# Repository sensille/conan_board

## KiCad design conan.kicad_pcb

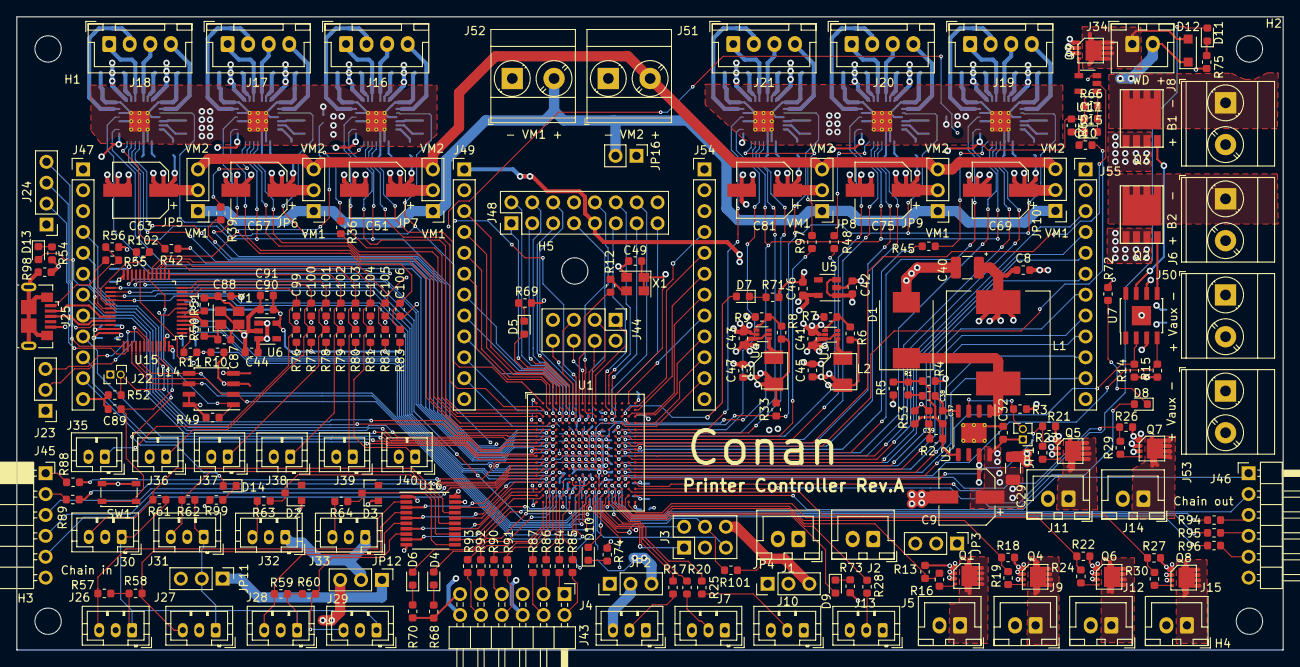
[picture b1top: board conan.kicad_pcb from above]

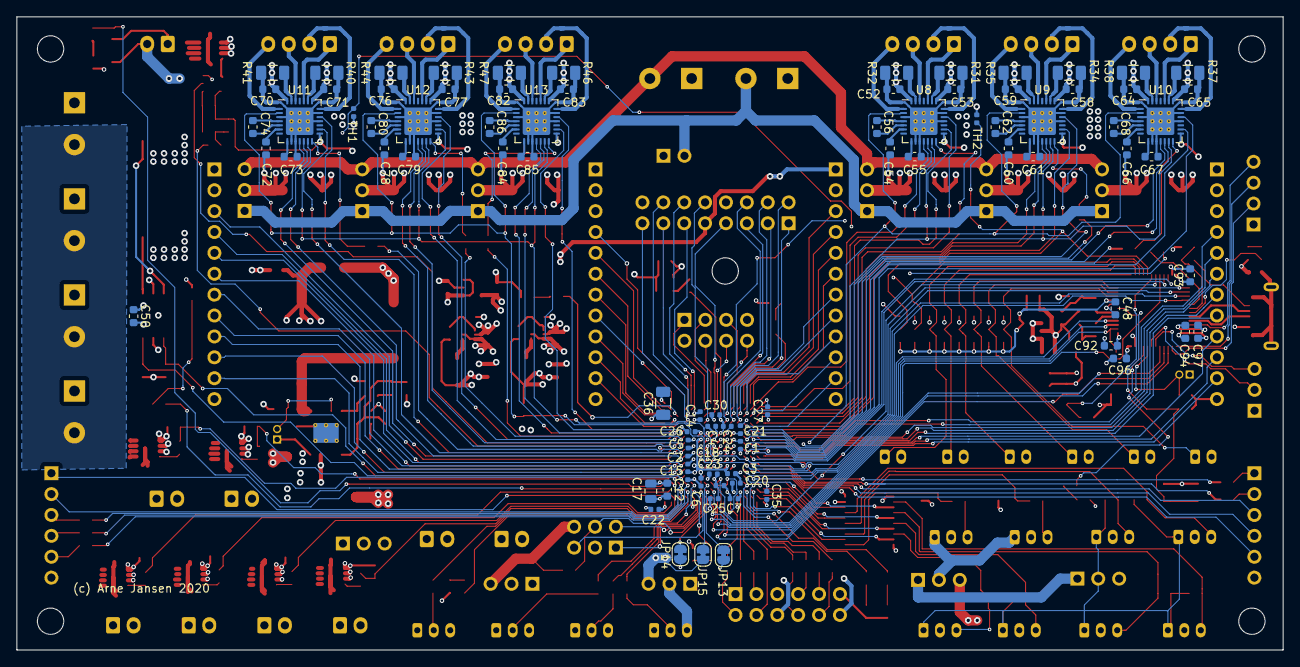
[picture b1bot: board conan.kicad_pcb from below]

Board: 4 copper layers, 154.0 x 77.0 mm, 320 parts (83 on the bottom side), 338 nets.

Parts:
C1, C2, C3, C4, C5, C6, C7, C14, C15, C21, C35: 10nF; C_0402_1005Metric
C8, C10, C11, C12, C42, C44, C46, C48, C91: 1uF; C_0603_1608Metric
C9, C51, C57, C63, C69, C75, C81: 100uF/50V/lowESR; CP_Elec_6.3x5.9
C17: 10uF; C_0805_2012Metric
C18, C20, C22, C23, C24, C25, C26, C27, C30: 100nF; C_0402_1005Metric
C29: 10uF/ceramic/50V/8mOhm; C_1206_3216Metric
C32: 220nF/50V; C_0603_1608Metric
C36: 22uF; C_1206_3216Metric
C37: 1.2nF; C_0603_1608Metric
C38: 68nF; C_0603_1608Metric
C39: 15nF; C_0603_1608Metric
C40: 68uF/tantalum/6.3V/100mOhm; C_1210_3225Metric
C41, C43: 4.7uF/10V/ceramic; C_0603_1608Metric
C45, C47: 22uF/6.3V/4mOhm/ceramic; C_0603_1608Metric
C49, C90: 10nF; C_0603_1608Metric
C50, C92, C93, C94, C96: 100nF; C_0603_1608Metric
C52, C53, C58, C59, C64, C65, C70, C71, C76, C77, C82, C83: 100nF/50V; C_0603_1608Metric
C54, C60, C66, C72, C78, C84: 100nF/16V; C_0603_1608Metric
C55, C61, C67, C73, C79, C85, C99, C100, C101, C102, C103, C104, C105, C106: 2.2uF; C_0603_1608Metric
C56, C62, C68, C74, C80, C86: 22nF/50V; C_0603_1608Metric
C87, C88: 10pF; C_0603_1608Metric
C89: 0.1uF; C_0603_1608Metric
C97: 4.7uF; C_0603_1608Metric
D1: MBRS540T3G; D_SMC
D2, D3: 5V; D_SOT-23_ANK
D4, D5, D6, D7, D8, D9, D10, D11, D13, D14: LED; LED_0603_1608Metric
D12: DSS12UTR; D_SOD-123F
D15: CDBU40; D_0603_1608Metric
H1, H2, H3, H4, H5: MountingHole; MountingHole_3.2mm_M3
J1, J2, J5, J9, J11, J12, J14, J15, J34: JST XH 2; JST_XH_B02B-XH-A_1x02_P2.50mm_Vertical
J3: PinH 2x3; PinHeader_2x03_P2.54mm_Vertical
J4, J7, J10, J13, J26, J27, J28, J29, J30, J31, J32, J33: JST PH 3; JST_PH_B3B-PH-K_1x03_P2.00mm_Vertical
J6, J8, J50, J51, J52, J53: ST 2; TerminalBlock_Phoenix_MKDS-3-2-5.08_1x02_P5.08mm_Horizontal
J16, J17, J18, J19, J20, J21: Stepper; JST_XH_B04B-XH-A_1x04_P2.50mm_Vertical
J22: PinHS 2; PinHeader_1x02_P1.27mm_Vertical
J23: PinH 3; PinHeader_1x03_P2.54mm_Vertical
J24: PinH 4; PinHeader_1x04_P2.54mm_Vertical
J25: USB_B_Micro; USB_Micro-B_GCT_USB3076-30-A
J35, J36, J37, J38, J39, J40: JST PH 2; JST_PH_B2B-PH-K_1x02_P2.00mm_Vertical
J43: PinH 2x6; PinHeader_2x06_P2.54mm_Horizontal
J44: ESP8266; PinHeader_2x04_P2.54mm_Vertical
J45: PinHHF 6; PinSocket_1x06_P2.54mm_Horizontal
J46: PinHH 6; PinHeader_1x06_P2.54mm_Horizontal
J47, J49, J54, J55: PinH 12; PinHeader_1x12_P2.54mm_Vertical
J48: PinH 2x8; PinHeader_2x08_P2.54mm_Vertical
JP1: Jumper_NC_Small; PinHeader_1x02_P1.27mm_Vertical
JP2, JP3, JP4, JP5, JP6, JP7, JP8, JP9, JP10, JP11, JP12: PinH 3; PinHeader_1x03_P2.54mm_Vertical
JP13, JP14, JP15: SolderJumper-2_P1.3mm_Bridged_RoundedPad1.0x1.5mm
JP16: PinH 2; PinHeader_1x02_P2.54mm_Vertical
L1: 22uH; L_Wuerth_WE-PD-Typ-LS
L2, L3: 1uH/10mOhm; SPM4012-LR
Q1, Q4, Q5, Q6, Q7, Q8, Q9: AON7524; FET_DGS_DFN3x3A_8L_EP1_P
Q2, Q3: TPH1R405PL; TPH1R405PL_SGD
R1: 1.1k; R_0603_1608Metric
R2: 240; R_0603_1608Metric
R3, R13, R14, R15, R18, R21, R22, R26, R27, R33, R65, R101: 10k; R_0603_1608Metric
R4: 5.1k; R_0603_1608Metric
R5: 680; R_0603_1608Metric
R6: 83.3k; R_0603_1608Metric
R7, R52: 100k; R_0603_1608Metric
R8: 435k; R_0603_1608Metric
R9: 97.6k; R_0603_1608Metric
R10, R11, R49, R76, R77, R78, R79, R80, R81, R82, R83: 4.7k; R_0603_1608Metric
R12, R16, R19, R23, R24, R29, R30, R84, R85, R86, R87, R88, R89, R90, R91, R92, R93, R94, R95, R96, R102: 22; R_0603_1608Metric
R17, R20, R25, R28: 220; R_0603_1608Metric
R31, R32, R34, R35, R37, R38, R40, R41, R43, R44, R46, R47: 100m; R_1206_3216Metric
R36, R39, R42, R45, R48, R54, R63, R64, R68, R69, R70, R71, R72, R73, R74, R75, R97, R99: 1k; R_0603_1608Metric
R50, R51: 0; R_0603_1608Metric
R53, R56: 220k; R_0603_1608Metric
R55: 330k; R_0603_1608Metric
R57, R58, R59, R60, R61, R62: 2.2k; R_0603_1608Metric
R66: 1M; R_0603_1608Metric
R98: 100; R_0603_1608Metric
SW1: Reset; SW_SPST_PTS810
TH1, TH2: NTC_100k; R_0402_1005Metric
U1: ECP5U12_CABGA256; BGA-256_14.0x14.0mm_Layout16x16_P0.8mm_Ball0.45mm_Pad0.32mm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
U2: L7986; HSOP-8-1EP_3.9x4.9mm_P1.27mm_EP2.41x3.1mm_ThermalVias
U3, U4: TLV62569; SOT-563
U5: LP5907MFX-2.5; SOT-23-5
U6: LP5907MFX-3.3; SOT-23-5
U7: MIC4127; SOIC-8-1EP_3.9x4.9mm_P1.27mm_EP2.35x2.35mm
U8, U9, U10, U11, U12, U13: TMC2209; QFN-28-1EP_5x5mm_P0.5mm_EP3.35x3.35mm_ThermalVias
U14: AT25xxx; SOIC-8_3.9x4.9mm_P1.27mm
U15: STM32F070CBTx; LQFP-48_7x7mm_P0.5mm
U16: 74VLX244; TSSOP-20_4.4x6.5mm_P0.65mm
U17: MC74VHC1G132; SOT-23-5
X1: ASE-50MHz; Oscillator_SMD_Abracon_ASE-4Pin_3.2x2.5mm
Y1: 16MHz; Crystal_SMD_SeikoEpson_TSX3225-4Pin_3.2x2.5mm

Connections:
+1V1: C1.1, C4.1, C7.1, C18.1, C20.1, C22.1, C23.1, C25.1, C45.1, L2.2, R6.1, U1.G6, U1.G7, U1.G9, U1.L8, U1.L9, U1.L10
+2V5: C3.1, C6.1, C12.1, C15.1, C17.1, C46.1, U1.G11, U1.L7, U5.5
+3V3: C2.1, C5.1, C11.1, C14.1, C21.1, C24.1, C26.1, C27.1, C30.1, C35.1, C36.1, C47.1, C49.1, C92.1, C93.1, C94.1, C96.1, C97.1, J3.6, J22.1, J43.6, J43.12, J44.7, J47.3, J48.16, J54.3, JP2.3, JP4.3, JP11.3, JP15.1, L3.2, R8.1, R10.2, R33.2, R49.1, R65.1, R66.1, R101.2, U1.F6, U1.F7, U1.F10, U1.F11, U1.H6, U1.H7, U1.H11, U1.J6, U1.J7, U1.J11, U1.K11, U1.L6, U1.L11, U8.15, U9.15, U10.15, U11.15, U12.15, U13.15, U14.3, U14.7, U14.8, U15.1, U15.24, U15.36, U15.48, U16.20, U17.5, X1.1, X1.4
+5V: C8.1, C39.1, C40.1, C41.1, C42.1, C43.1, C44.1, C50.1, D12.1, J1.1, J2.1, J34.2, J48.9, J49.1, J55.1, JP2.1, JP3.3, JP4.1, JP11.1, JP12.1, L1.2, R4.1, R53.1, U3.3, U3.5, U4.3, U4.5, U5.1, U5.3, U6.1, U6.3, U7.6
+VM1: J52.2, JP5.1, JP6.1, JP7.1, JP8.1, JP9.1, JP10.1, JP16.2
+VM2: J51.2, JP5.3, JP6.3, JP7.3, JP8.3, JP9.3, JP10.3
+Vaux: C9.1, C29.1, C32.1, J6.2, J8.2, J11.2, J14.2, J47.1, J50.2, J53.2, J54.1, JP1.1, JP3.1, JP12.3, JP16.1, U2.8
/FPGA/TCK: J3.4, R101.1, U1.T10
/FPGA/TDI: J3.2, U1.R11
/FPGA/TDO: J3.5, U1.M10
/FPGA/TMS: J3.1, U1.T11
/Stepper/Stepper 1/OA1: J18.1, U10.24
/Stepper/Stepper 1/OA2: J18.2, U10.21
/Stepper/Stepper 1/OB1: J18.3, U10.26
/Stepper/Stepper 1/OB2: J18.4, U10.1
/Stepper/Stepper 1/VM: C63.1, C64.1, C65.1, C66.2, JP5.2, U10.22, U10.28
/Stepper/Stepper 2/OA1: J17.1, U9.24
/Stepper/Stepper 2/OA2: J17.2, U9.21
/Stepper/Stepper 2/OB1: J17.3, U9.26
/Stepper/Stepper 2/OB2: J17.4, U9.1
/Stepper/Stepper 2/VM: C57.1, C58.1, C59.1, C60.2, JP6.2, U9.22, U9.28
/Stepper/Stepper 3/OA1: J16.1, U8.24
/Stepper/Stepper 3/OA2: J16.2, U8.21
/Stepper/Stepper 3/OB1: J16.3, U8.26
/Stepper/Stepper 3/OB2: J16.4, U8.1
/Stepper/Stepper 3/VM: C51.1, C52.1, C53.1, C54.2, JP7.2, U8.22, U8.28
/Stepper/Stepper 4/OA1: J21.1, U13.24
/Stepper/Stepper 4/OA2: J21.2, U13.21
/Stepper/Stepper 4/OB1: J21.3, U13.26
/Stepper/Stepper 4/OB2: J21.4, U13.1
/Stepper/Stepper 4/VM: C81.1, C82.1, C83.1, C84.2, JP8.2, U13.22, U13.28
/Stepper/Stepper 5/OA1: J20.1, U12.24
/Stepper/Stepper 5/OA2: J20.2, U12.21
/Stepper/Stepper 5/OB1: J20.3, U12.26
/Stepper/Stepper 5/OB2: J20.4, U12.1
/Stepper/Stepper 5/VM: C75.1, C76.1, C77.1, C78.2, JP9.2, U12.22, U12.28
/Stepper/Stepper 6/OA1: J19.1, U11.24
/Stepper/Stepper 6/OA2: J19.2, U11.21
/Stepper/Stepper 6/OB1: J19.3, U11.26
/Stepper/Stepper 6/OB2: J19.4, U11.1
/Stepper/Stepper 6/VM: C69.1, C70.1, C71.1, C72.2, JP10.2, U11.22, U11.28
/mcu/RX: J24.2, U15.38
/mcu/SWDIO: J24.4, U15.34
/mcu/TX-SWCLK: J24.3, U15.37
ADC0: C99.1, J35.1, R76.2, U15.10
ADC1: C100.1, J36.1, R77.2, U15.11
ADC2: C101.1, J37.1, R78.2, U15.12
ADC3: C102.1, J38.1, R79.2, U15.13
ADC4: C103.1, J39.1, R80.2, U15.14
ADC5: C104.1, J40.1, R81.2, U15.15
ADC6: C105.1, R82.2, TH1.2, U15.16
ADC7: C106.1, R83.2, TH2.2, U15.17
CLK: U1.J4, U8.13, U9.13, U10.13, U11.13, U12.13, U13.13
CLK_48MHz: R102.1, U1.A7
CLK_50MHz: R12.1, U1.C8
DIAG1: U1.F4, U10.11
DIAG2: U1.D1, U9.11
DIAG3: U1.A2, U8.11
DIAG4: U1.E15, U13.11
DIAG5: U1.G14, U12.11
DIAG6: U1.J16, U11.11
DIR1: U1.H4, U10.19
DIR2: U1.E4, U9.19
DIR3: U1.C2, U8.19
DIR4: U1.E16, U13.19
DIR5: U1.F15, U12.19
DIR6: U1.H15, U11.19
DONE: U1.P9, U15.4
ENDSTOP1: U1.M4, U16.18
ENDSTOP2: U1.P1, U16.16
ENDSTOP3: U1.R1, U16.14
ENDSTOP4: U1.P3, U16.12
ENDSTOP5: U1.M2, U16.3
ENDSTOP6: U1.N1, U16.5
ENDSTOP7: U1.P2, U16.7
ENDSTOP8: U1.R2, U16.9
ENN: R33.1, U1.K4, U8.2, U9.2, U10.2, U11.2, U12.2, U13.2
ESP_EN: J44.3, U1.B10
ESP_FLASH: J44.6, U1.A8
ESP_GPIO2: J44.4, U1.A9
ESP_RST: J44.5, U1.B7
ESP_RX: J44.8, U1.D7
ESP_TX: J44.1, U1.A10
FPGA1: U1.J3, U15.21
FPGA2: U1.H3, U15.22
FPGA3: U1.K3, U15.25
FPGA4: U1.L3, U15.26
FPGA5: U1.L4, U15.27
FPGA6: U1.M3, U15.28
GND: C1.2, C2.2, C3.2, C4.2, C5.2, C6.2, C7.2, C8.2, C9.2, C12.2, C14.2, C15.2, C17.2, C18.2, C20.2, C21.2, C22.2, C23.2, C24.2, C25.2, C26.2, C27.2, C29.2, C30.2, C32.2, C35.2, C36.2, C40.2, C41.2, C42.2, C43.2, C44.2, C45.2, C46.2, C47.2, C48.2, C49.2, C50.2, C51.2, C52.2, C53.2, C55.2, C57.2, C58.2, C59.2, C61.2, C63.2, C64.2, C65.2, C67.2, C69.2, C70.2, C71.2, C73.2, C75.2, C76.2, C77.2, C79.2, C81.2, C82.2, C83.2, C85.2, C87.2, C88.2, C89.2, C90.2, C91.2, C92.2, C93.2, C94.2, C96.2, C97.2, C99.2, C100.2, C101.2, C102.2, C103.2, C104.2, C105.2, C106.2, D1.2, D2.2, D3.2, J1.2, J2.2, J3.3, J4.1, J7.1, J10.1, J13.1, J23.1, J24.1, J25.5, J26.2, J27.2, J28.2, J29.2, J30.2, J31.2, J32.2, J33.2, J35.2, J36.2, J37.2, J38.2, J39.2, J40.2, J43.5, J43.11, J44.2, J45.6, J46.6, J47.2, J47.12, J48.8, J49.2, J49.12, J50.1, J51.1, J52.1, J53.1, J54.2, J54.12, J55.2, J55.12, JP13.1, JP14.1, Q1.3, Q2.1, Q3.1, Q4.3, Q5.3, Q6.3, Q7.3, Q8.3, Q9.3, R3.2, R5.2, R7.2, R9.2, R13.2, R14.2, R15.2, R18.2, R21.2, R22.2, R26.2, R27.2, R31.2, R32.2, R34.2, R35.2, R37.2, R38.2, R40.2, R41.2, R43.2, R44.2, R46.2, R47.2, R52.1, R54.1, R56.2, R68.1, R69.1, R70.1, R71.1, R72.1, R73.1, R74.1, R75.1, R98.1, R99.1, SW1.2, TH1.1, TH2.1, U1.A1, U1.A16, U1.D2, U1.D15, U1.F8, U1.F9, U1.G8, U1.G10, U1.H1, U1.H8, U1.H9, U1.H10, U1.H16, U1.J8, U1.J9, U1.J10, U1.K6, U1.K7, U1.K8, U1.K9, U1.K10, U1.N2, U1.N15, U1.T1, U1.T5, U1.T12, U1.T16, U2.7, U2.9, U3.2, U4.2, U5.2, U6.2, U7.3, U7.9, U8.3, U8.9, U8.10, U8.18, U8.20, U8.29, U9.3, U9.9, U9.10, U9.18, U9.20, U9.29, U10.3, U10.9, U10.10, U10.18, U10.20, U10.29, U11.3, U11.9, U11.10, U11.18, U11.20, U11.29, U12.3, U12.9, U12.10, U12.18, U12.20, U12.29, U13.3, U13.9, U13.10, U13.18, U13.20, U13.29, U14.4, U15.8, U15.23, U15.35, U15.47, U16.1, U16.10, U16.19, U17.3, X1.2, Y1.2, Y1.4
HOLDN: U1.N8, U15.19
INDEX1: U1.F3, U10.12
INDEX2: U1.D3, U9.12
INDEX3: U1.B2, U8.12
INDEX4: U1.E14, U13.12
INDEX5: U1.G13, U12.12
INDEX6: U1.J13, U11.12
INITN: U1.T9, U15.3
LED1: D4.2, U1.P4
LED2: D5.2, U1.B5
LED3: D6.2, U1.N3
LED4: D7.2, U1.C14
LED5: D8.2, U1.P16
LED6: D9.2, U1.T13
LED7: D10.2, U1.P12
LED8: D11.2, U1.N16
LED9: D13.2, U15.31
LED10: D14.2, U15.45
unnamed: C10.1, D15.1, R65.2
unnamed: C11.2, D15.2, R66.2, U17.1
unnamed: C37.1, C38.1, U2.4
unnamed: C37.2, R1.2, R2.2, R4.2, R5.1, R53.2, U2.5
unnamed: C38.2, R1.1
unnamed: C39.2, R2.1
unnamed: C54.1, U8.6
unnamed: C55.1, U8.8
unnamed: C56.1, U8.4
unnamed: C56.2, U8.5
unnamed: C60.1, U9.6
unnamed: C61.1, U9.8
unnamed: C62.1, U9.4
unnamed: C62.2, U9.5
unnamed: C66.1, U10.6
unnamed: C67.1, U10.8
unnamed: C68.1, U10.4
unnamed: C68.2, U10.5
unnamed: C72.1, U11.6
unnamed: C73.1, U11.8
unnamed: C74.1, U11.4
unnamed: C74.2, U11.5
unnamed: C78.1, U12.6
unnamed: C79.1, U12.8
unnamed: C80.1, U12.4
unnamed: C80.2, U12.5
unnamed: C84.1, U13.6
unnamed: C85.1, U13.8
unnamed: C86.1, U13.4
unnamed: C86.2, U13.5
unnamed: C87.1, R50.2, Y1.1
unnamed: C88.1, R51.2, Y1.3
unnamed: C89.1, SW1.1, U15.7
unnamed: D1.1, L1.1, U2.1
unnamed: D2.1, R63.1, U16.13
unnamed: D3.1, R64.1, U16.11
unnamed: D4.1, R68.2
unnamed: D5.1, R69.2
unnamed: D6.1, R70.2
unnamed: D7.1, R71.2
unnamed: D8.1, R72.2
unnamed: D9.1, R73.2
unnamed: D10.1, R74.2
unnamed: D11.1, R75.2
unnamed: D12.2, J34.1, Q9.1
unnamed: D13.1, R54.2
unnamed: D14.1, R99.2
unnamed: J4.2, R17.1
unnamed: J4.3, J7.3, JP2.2
unnamed: J5.1, Q1.1
unnamed: J6.1, Q2.3
unnamed: J7.2, R20.1
unnamed: J8.1, Q3.3
unnamed: J9.1, Q4.1
unnamed: J10.2, R25.1
unnamed: J10.3, J13.3, JP4.2
unnamed: J11.1, Q5.1
unnamed: J12.1, Q6.1
unnamed: J5.2, J9.2, J12.2, J15.2, JP3.2
unnamed: J13.2, R28.1
unnamed: J14.1, Q7.1
unnamed: J15.1, Q8.1
unnamed: J22.2, R52.2, U15.44
unnamed: J23.2, U15.43
unnamed: J23.3, U15.42
unnamed: J25.1, R55.1
unnamed: J25.2, U15.32
unnamed: J25.3, U15.33
unnamed: J25.6, R98.2
unnamed: J26.1, J27.1, J28.1, J29.1, J30.1, J31.1, JP11.2, R57.1, R58.1, R59.1, R60.1, R61.1, R62.1
unnamed: J26.3, R57.2, U16.2
unnamed: J27.3, R58.2, U16.4
unnamed: J28.3, R59.2, U16.6
unnamed: J29.3, R60.2, U16.8
unnamed: J30.3, R61.2, U16.17
unnamed: J31.3, R62.2, U16.15
unnamed: J32.1, J33.1, JP12.2
unnamed: J32.3, R63.2
unnamed: J33.3, R64.2
unnamed: J43.1, R84.1
unnamed: J43.2, R85.1
unnamed: J43.3, R86.1
unnamed: J43.4, R87.1
unnamed: J43.7, R90.1
unnamed: J43.8, R91.1
unnamed: J43.9, R92.1
unnamed: J43.10, R93.1
unnamed: J45.1, R88.1
unnamed: J45.2, R89.1
unnamed: J46.3, R94.2
unnamed: J46.4, R95.2
unnamed: J46.5, R96.2
unnamed: JP1.2, R3.1, U2.3
unnamed: JP13.2, U1.P10
unnamed: JP14.2, U1.R10
unnamed: JP15.2, U1.N10
unnamed: L2.1, U3.4
unnamed: L3.1, U4.4
unnamed: Q1.2, R16.1
unnamed: Q2.2, U7.5
unnamed: Q3.2, U7.7
unnamed: Q4.2, R19.1
unnamed: Q5.2, R23.1
unnamed: Q6.2, R24.1
unnamed: Q7.2, R29.1
unnamed: Q8.2, R30.1
unnamed: Q9.2, U17.4
unnamed: R6.2, R7.1, U3.1
unnamed: R8.2, R9.1, U4.1
unnamed: R12.2, X1.3
unnamed: R31.1, U8.23
unnamed: R32.1, U8.27
unnamed: R34.1, U9.23
unnamed: R35.1, U9.27
unnamed: R36.2, U8.14
unnamed: R37.1, U10.23
unnamed: R38.1, U10.27
unnamed: R39.2, U9.14
unnamed: R40.1, U11.23
unnamed: R41.1, U11.27
unnamed: R42.2, U10.14
unnamed: R43.1, U12.23
unnamed: R44.1, U12.27
unnamed: R45.2, U11.14
unnamed: R46.1, U13.23
unnamed: R47.1, U13.27
unnamed: R48.2, U12.14
unnamed: R49.2, U14.1, U15.18
unnamed: R50.1, U15.5
unnamed: R51.1, U15.6
unnamed: R55.2, R56.1, U15.30
unnamed: R97.2, U13.14
unnamed: R102.2, U15.29
PROGRAMN: R11.1, U1.R9, U15.2
PWM1: R14.1, U1.M16, U7.2
PWM2: R15.1, U1.M13, U7.4
PWM3: R21.1, R23.2, U1.M15
PWM4: R26.1, R29.2, U1.M14
PWM5: R13.1, R16.2, U1.T14
PWM6: R18.1, R19.2, U1.R15
PWM7: R22.1, R24.2, U1.T15
PWM8: R27.1, R30.2, U1.P15
PWM9: R17.2, U1.R12
PWM10: R20.2, U1.N12
PWM11: R25.2, U1.R13
PWM12: R28.2, U1.R14
SPI_MISO: U1.T7, U14.2, U15.40
SPI_MOSI: U1.T8, U14.5, U15.41
SPI_NSS: R10.1, R11.2, U1.P8, U15.20
SPI_SCK: U1.N9, U14.6, U15.39
STEP1: U1.G3, U10.16
STEP2: U1.E1, U9.16
STEP3: U1.B1, U8.16
STEP4: U1.E13, U13.16
STEP5: U1.F14, U12.16
STEP6: U1.H14, U11.16
UART1: R42.1, U1.G4
UART2: R39.1, U1.E3
UART3: R36.1, U1.C1
UART4: R97.1, U1.F16
UART5: R48.1, U1.F13
UART6: R45.1, U1.H13
VDDA: C48.1, C90.1, C91.1, R76.1, R77.1, R78.1, R79.1, R80.1, R81.1, R82.1, R83.1, U6.5, U15.9
WDEN: U1.G16, U17.2
WDI: C10.2, U1.G15
chain_in_in1: J45.5, U1.M1
chain_in_in2: J45.4, U1.L2
chain_in_in3: J45.3, U1.L1
chain_in_out1: R89.2, U1.K2
chain_in_out2: R88.2, U1.K1
chain_out_in1: J46.2, U1.N14
chain_out_in2: J46.1, U1.R16
chain_out_out1: R96.1, U1.P13
chain_out_out2: R95.1, U1.N13
chain_out_out3: R94.1, U1.P14
display1: J48.1, U1.A5
display2: J48.2, U1.C6
display3: J48.3, U1.B6
display4: J48.4, U1.D6
display5: J48.5, U1.A6
display6: J48.6, U1.C7
display7: J48.7, U1.C10
display8: J48.10, U1.D10
display9: J48.11, U1.B12
display10: J48.12, U1.A12
display11: J48.13, U1.B13
display12: J48.14, U1.C13
display13: J48.15, U1.D13
exp1_1: J47.4, U1.E2
exp1_2: J47.5, U1.F1
exp1_3: J47.6, U1.F2
exp1_4: J47.7, U1.G1
exp1_5: J47.8, U1.G2
exp1_6: J47.9, U1.H2
exp1_7: J47.10, U1.J1
exp1_8: J47.11, U1.J2
exp1_9: J49.11, U1.D4
exp1_10: J49.10, U1.C3
exp1_11: J49.9, U1.C4
exp1_12: J49.8, U1.C5
exp1_13: J49.7, U1.D5
exp1_14: J49.6, U1.B3
exp1_15: J49.5, U1.A3
exp1_16: J49.4, U1.B4
exp1_17: J49.3, U1.A4
exp2_1: J54.4, U1.A13
exp2_2: J54.5, U1.B15
exp2_3: J54.6, U1.B16
exp2_4: J54.7, U1.C15
exp2_5: J54.8, U1.A15
exp2_6: J54.9, U1.C16
exp2_7: J54.10, U1.D16
exp2_8: J54.11, U1.D14
exp2_9: J55.11, U1.L14
exp2_10: J55.10, U1.L15
exp2_11: J55.9, U1.L13
exp2_12: J55.8, U1.L16
exp2_13: J55.7, U1.K14
exp2_14: J55.6, U1.K15
exp2_15: J55.5, U1.K13
exp2_16: J55.4, U1.K16
exp2_17: J55.3, U1.J15
pmod1_1: R84.2, U1.R5
pmod1_2: R85.2, U1.T6
pmod1_3: R86.2, U1.T4
pmod1_4: R87.2, U1.R4
pmod2_1: R90.2, U1.R3
pmod2_2: R91.2, U1.T3
pmod2_3: R92.2, U1.T2
pmod2_4: R93.2, U1.N4

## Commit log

2019-11-16 Last version with tmc2660
2019-11-17 Replaced TMC2660 by TMC2209
2019-11-17 MOSFETs chosen.
2019-11-17 Annotated values in Power sheet
2019-11-17 Changed misc FETs from SIA440DJ to AON7524
2019-11-17 Tidy up top sheet
2019-11-18 fixed some ERC warnings
2019-11-18 swapped ECP5 symbol for own
2019-11-19 Add missing project file
2019-11-19 ECR done.
2019-11-20 some package assignments
2019-11-23 Footprints done
2019-11-23 Netlist import to PCB
2019-11-23 Recovery after crash, replace double row pin header for expansion by 2 separate single row headers
2019-11-23 rough placement
2019-11-23 better footprints for restistors and capacitors
2019-11-23 More footprint updates, removed individual ENN pullups for drivers
2019-11-24 routing sketch for stepper driver
2019-11-24 rough reassignment of fpga-pads to account for the direction in which the wires go. Only assign to outer 4 rings for easier escape routing.
2019-11-24 more reassignments
2019-11-24 clean start for escape routing
2019-11-25 some escape routing
2019-11-26 more escape routing
2019-11-26 Escape routing done.
2019-11-27 snapshot before going from 0402 to 0603
2019-11-27 fixed an error in tmc2209 schematic, finished routing one driver
2019-11-28 2./3. driver in progress
2019-11-30 stepper driver done
2019-11-30 dc-dc converter
2019-12-01 placement roughly done
2019-12-01 routing snapshot
2019-12-01 reassign some FPGA pins for ease of routing
2019-12-03 more routing
2019-12-08 power routing done
2019-12-09 more remapping/routing
2019-12-10 all traces connected
2019-12-12 DRC done. Silk adjusted.
2019-12-12 beautify
2019-12-12 more beautification
2019-12-12 some nitpicks
2019-12-12 nitpicks, usb shield via R to GND
2019-12-12 amend last commit
2019-12-12 added some labels to silk
2019-12-12 remove voltage divider for uart, as PA15 is 5V-tolerant anyway.
2019-12-12 move 5th mounting hole more to center of board
2019-12-12 first prototype version
2020-01-09 snapshot
2020-01-10 small fix, ordered this version
2020-01-11 consolidate values to get a clearer BOM
2020-06-11 add sym-lib-table with relative paths, fixes missing symbols in eeschema
2021-03-19 added pdf export of schematics
